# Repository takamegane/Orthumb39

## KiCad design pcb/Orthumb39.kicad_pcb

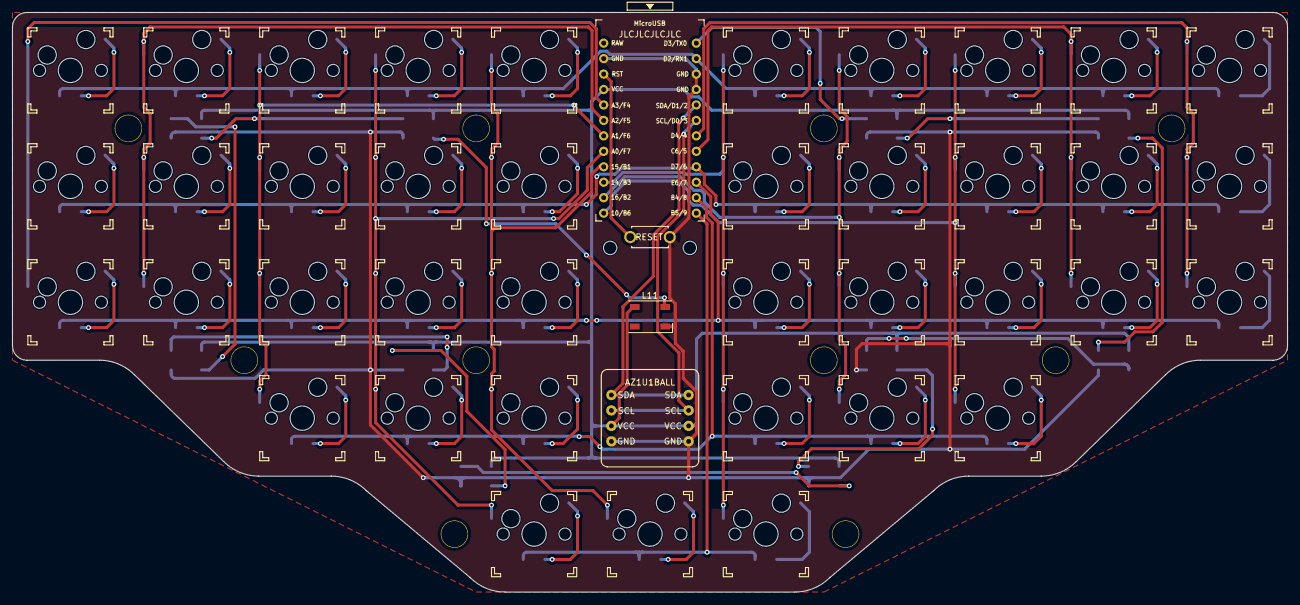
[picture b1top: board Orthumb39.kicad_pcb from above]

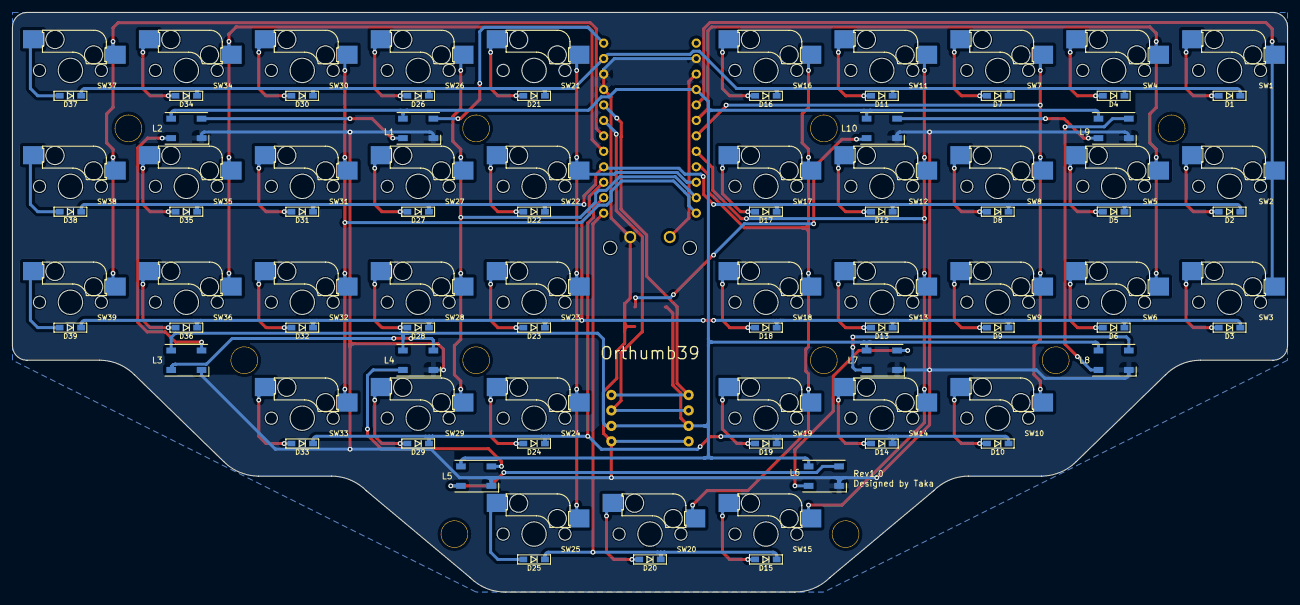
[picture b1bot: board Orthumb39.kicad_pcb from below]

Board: 2 copper layers, 209.6 x 95.2 mm, 104 parts (11 on the bottom side), 70 nets.

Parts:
AZ1U1BALL: AZ1UBALL
D1, D2, D3, D4, D5, D6, D7, D8, D9, D10, D11, D12, D13, D14, D15, D16, D17, D18, D19, D20, D21, D22, D23, D24, D25, D26, D27, D28, D29, D30, D31, D32, D33, D34, D35, D36, D37, D38, D39: D; Diode_SMD
L1, L2, L3, L4, L5, L6, L7, L8, L9, L10, L11: WS2812B; LED_WS2812B-PLCC4
Ref**: Val**; m2_Spacer_Hole
Ref**#2, Ref**#7: Val**; m2_Screw_Hole
Ref**#3, Ref**#4, Ref**#5, Ref**#6, Ref**#8, Ref**#9, Ref**#10, Ref**#11, Ref**#12: Val**; m2_Spacer_Hole
SW1, SW2, SW3, SW4, SW5, SW6, SW7, SW8, SW9, SW10, SW11, SW12, SW13, SW14, SW15, SW16, SW17, SW18, SW19, SW20, SW21, SW22, SW23, SW24, SW25, SW26, SW27, SW28, SW29, SW30, SW31, SW32, SW33, SW34, SW35, SW36, SW37, SW38, SW39: SW_PUSH; CherryMX_Hotswap_1uex
SW40: SW_PUSH; ResetSW
U1: ProMicro; ProMicro_v3.5

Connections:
Col0: SW1.1, SW2.1, SW3.1, U1.20 (F4/A3)
Col1: SW4.1, SW5.1, SW6.1, U1.19 (F5/A2)
Col2: SW7.1, SW8.1, SW9.1, SW10.1, U1.18 (F6/A1)
Col3: SW11.1, SW12.1, SW13.1, SW14.1, SW15.1, U1.17 (F7/A0)
Col4: SW16.1, SW17.1, SW18.1, SW19.1, SW20.1, U1.16 (B1/15)
Col5: SW21.1, SW22.1, SW23.1, SW24.1, SW25.1, U1.15 (B3/14)
Col6: SW26.1, SW27.1, SW28.1, SW29.1, U1.14 (B2/16)
Col7: SW30.1, SW31.1, SW32.1, SW33.1, U1.13 (B6/10)
Col8: SW34.1, SW35.1, SW36.1, U1.8 (5/C6)
Col9: SW37.1, SW38.1, SW39.1, U1.7 (4/D4)
GND: AZ1U1BALL.4 (GND), L1.3 (VSS), L2.3 (VSS), L3.3 (VSS), L4.3 (VSS), L5.3 (VSS), L6.3 (VSS), L7.3 (VSS), L8.3 (VSS), L9.3 (VSS), L10.3 (VSS), L11.3 (VSS), SW40.2, U1.3 (GND), U1.4 (GND), U1.23 (GND)
LED: L1.4 (DIN), U1.1 (TX0/D3)
unnamed: D1.2 (A), SW1.2
unnamed: D2.2 (A), SW2.2
unnamed: D3.2 (A), SW3.2
unnamed: D4.2 (A), SW4.2
unnamed: D5.2 (A), SW5.2
unnamed: D6.2 (A), SW6.2
unnamed: D7.2 (A), SW7.2
unnamed: D8.2 (A), SW8.2
unnamed: D9.2 (A), SW9.2
unnamed: D10.2 (A), SW10.2
unnamed: D11.2 (A), SW11.2
unnamed: D12.2 (A), SW12.2
unnamed: D13.2 (A), SW13.2
unnamed: D14.2 (A), SW14.2
unnamed: D15.2 (A), SW15.2
unnamed: D16.2 (A), SW16.2
unnamed: D17.2 (A), SW17.2
unnamed: D18.2 (A), SW18.2
unnamed: D19.2 (A), SW19.2
unnamed: D20.2 (A), SW20.2
unnamed: D21.2 (A), SW21.2
unnamed: D22.2 (A), SW22.2
unnamed: D23.2 (A), SW23.2
unnamed: D24.2 (A), SW24.2
unnamed: D25.2 (A), SW25.2
unnamed: D26.2 (A), SW26.2
unnamed: D27.2 (A), SW27.2
unnamed: D28.2 (A), SW28.2
unnamed: D29.2 (A), SW29.2
unnamed: D30.2 (A), SW30.2
unnamed: D31.2 (A), SW31.2
unnamed: D32.2 (A), SW32.2
unnamed: D33.2 (A), SW33.2
unnamed: D34.2 (A), SW34.2
unnamed: D35.2 (A), SW35.2
unnamed: D36.2 (A), SW36.2
unnamed: D37.2 (A), SW37.2
unnamed: D38.2 (A), SW38.2
unnamed: D39.2 (A), SW39.2
unnamed: L1.2 (DOUT), L2.4 (DIN)
unnamed: L2.2 (DOUT), L3.4 (DIN)
unnamed: L3.2 (DOUT), L4.4 (DIN)
unnamed: L4.2 (DOUT), L5.4 (DIN)
unnamed: L5.2 (DOUT), L6.4 (DIN)
unnamed: L6.2 (DOUT), L7.4 (DIN)
unnamed: L7.2 (DOUT), L8.4 (DIN)
unnamed: L8.2 (DOUT), L9.4 (DIN)
unnamed: L9.2 (DOUT), L10.4 (DIN)
unnamed: L10.2 (DOUT), L11.4 (DIN)
Reset: SW40.1, U1.22 (RST)
Row0: D1.1 (K), D4.1 (K), D7.1 (K), D11.1 (K), D16.1 (K), D21.1 (K), D26.1 (K), D30.1 (K), D34.1 (K), D37.1 (K), U1.2 (RX1/D2)
Row1: D2.1 (K), D5.1 (K), D8.1 (K), D12.1 (K), D17.1 (K), D22.1 (K), D27.1 (K), D31.1 (K), D35.1 (K), D38.1 (K), U1.9 (6/D7)
Row2: D3.1 (K), D6.1 (K), D9.1 (K), D13.1 (K), D18.1 (K), D23.1 (K), D28.1 (K), D32.1 (K), D36.1 (K), D39.1 (K), U1.10 (7/E6)
Row3: D10.1 (K), D14.1 (K), D19.1 (K), D24.1 (K), D29.1 (K), D33.1 (K), U1.11 (8/B4)
Row4: D15.1 (K), D20.1 (K), D25.1 (K), U1.12 (9/B5)
SCL: AZ1U1BALL.2 (SCL), U1.6 (3/D0/SCL)
SDA: AZ1U1BALL.1 (SDA), U1.5 (2/D1/SDA)
VCC: AZ1U1BALL.3 (VCC), L1.1 (VDD), L2.1 (VDD), L3.1 (VDD), L4.1 (VDD), L5.1 (VDD), L6.1 (VDD), L7.1 (VDD), L8.1 (VDD), L9.1 (VDD), L10.1 (VDD), L11.1 (VDD), U1.21 (VCC)

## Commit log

2024-04-20 file add
    file add
2024-05-17 add acceleration mode
    加速度モード追加
2024-05-17 Create README.md
    加速モードについての説明
2024-05-17 Update orthumb39_vial.uf2
    スピード変更
2024-05-27 promicro firm update
    promicro用の加速モード追加
